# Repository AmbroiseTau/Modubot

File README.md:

<div style="display: flex; justify-content: center; margin: 0 auto; width: 100%;">
  
</div>

---

**Modubot** is a modular robotics platform built around **cube-shaped modules**, each with a **dedicated PCB** designed for specific functions. These modules can serve as **regional controllers**, **motor controllers**, **sensor modules**, or other customizable components, allowing for a **flexible and adaptable robotic system**. The entire project is based on **STM32 microcontrollers**.

<div style="display: flex; justify-content: center; margin: 0 auto; width: 100%;">

</div>

---

## **Goal:**

The vision for Modubot is to create a **flexible, modular platform** that promotes **hands-on learning** and **skill development**. By using **cube-based modules**, each with a unique **electronic function**, Modubot acts as a **test platform** for experimenting with:

- **Protocols**
- **Circuits**
- **PCB architecture**
- **Firmware**

This project is a chance to **apply and refine engineering knowledge** while exploring **creative possibilities in robotics**.

---

## **Roadmap:**
1. **✅ Design First Ever Module (General Purpose) - Accomplished**
2. **✅ Create a Simple 2-Wheel Robot with Remote Operation - Accomplished**
3. **✅ Write Firmware for CAN-FD, IMU, UART GPS**
4. **✅ Create a 2 Degrees of Freedom Arm**
5. **🔲 Design a Brushed/Stepper/BLDC Motor Controller Module (MCM)**
6. **🔲 Create a Miniature Buggy Rover**
7. **🔲 Design 2nd Version of the General Purpose Module (GPM)**
8. **🔲 Design Modular Drone (1x GPM + 4x MCM)**

---

## **Current Status:**

### **STAGE 2:**
The current phase features a **2-wheeled robot** designed as a **proof of concept**. It tests the **General Purpose Module (GPM v1)** along with:

- **SPI to NRF24L01** (used for remote control)
- **Servo control**

However, the **continuous servos** faced **tuning issues**, preventing the robot from driving straight, highlighting the need to shift towards **PID-controlled DC motors with encoders** for precise control.

<div style="display: flex; justify-content: center; margin: 0 auto; width: 100%;">

</div>

---

### **STAGE 1:**
The **first wave of designs** has been completed. The initial **PCB design** was kept **simple** to avoid unnecessary points of failure. It functions as intended, though there are some **design oversights**:

- It cannot handle **high current** (only 1-2 amps at 12V)
- Limited **resistance to back EMF**

These issues will be addressed in **version 2**, after learning more about system requirements.

The **3D-printed structure** has also been refined and is expected to remain unchanged unless major issues arise. For **quick connections** between modules and subcomponents (e.g., PCB bracket), **3D-printed Lego pins (scaled 1.25x)** are being used, and for more **permanent fixtures**, **M6 bolts** can be inserted in the same holes. Initially, **PETG** was used for printing, but due to **brittleness**, the material has been changed to **ABS**, which is more **ductile**.

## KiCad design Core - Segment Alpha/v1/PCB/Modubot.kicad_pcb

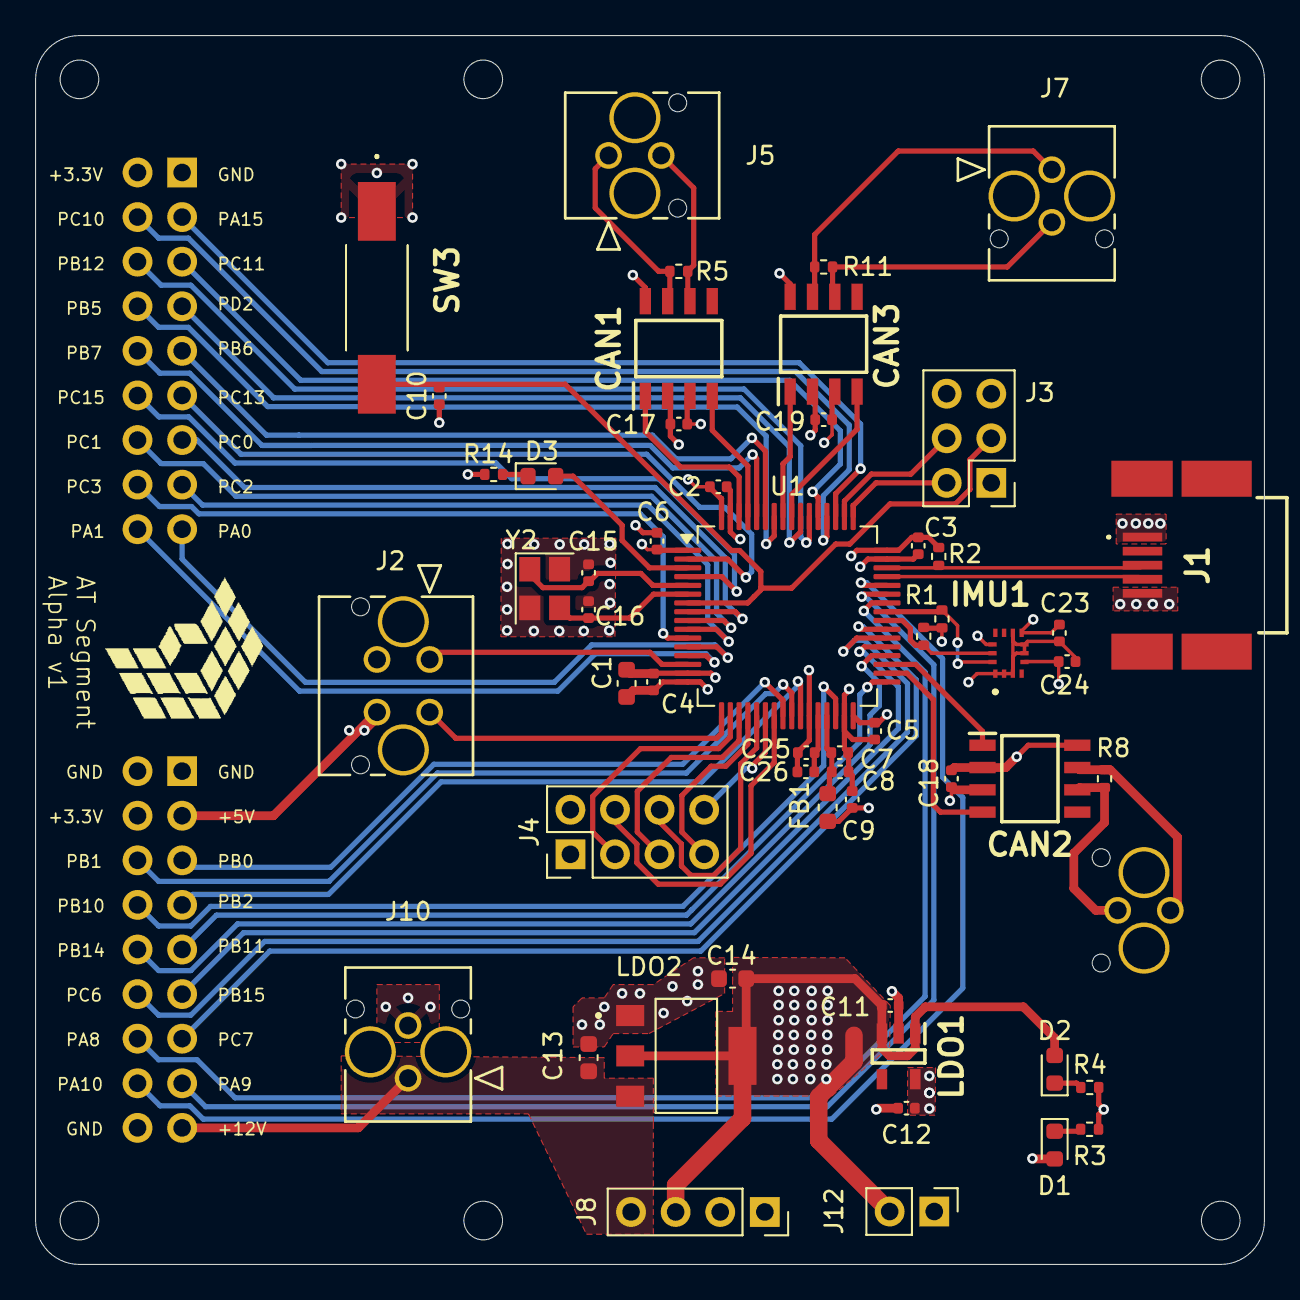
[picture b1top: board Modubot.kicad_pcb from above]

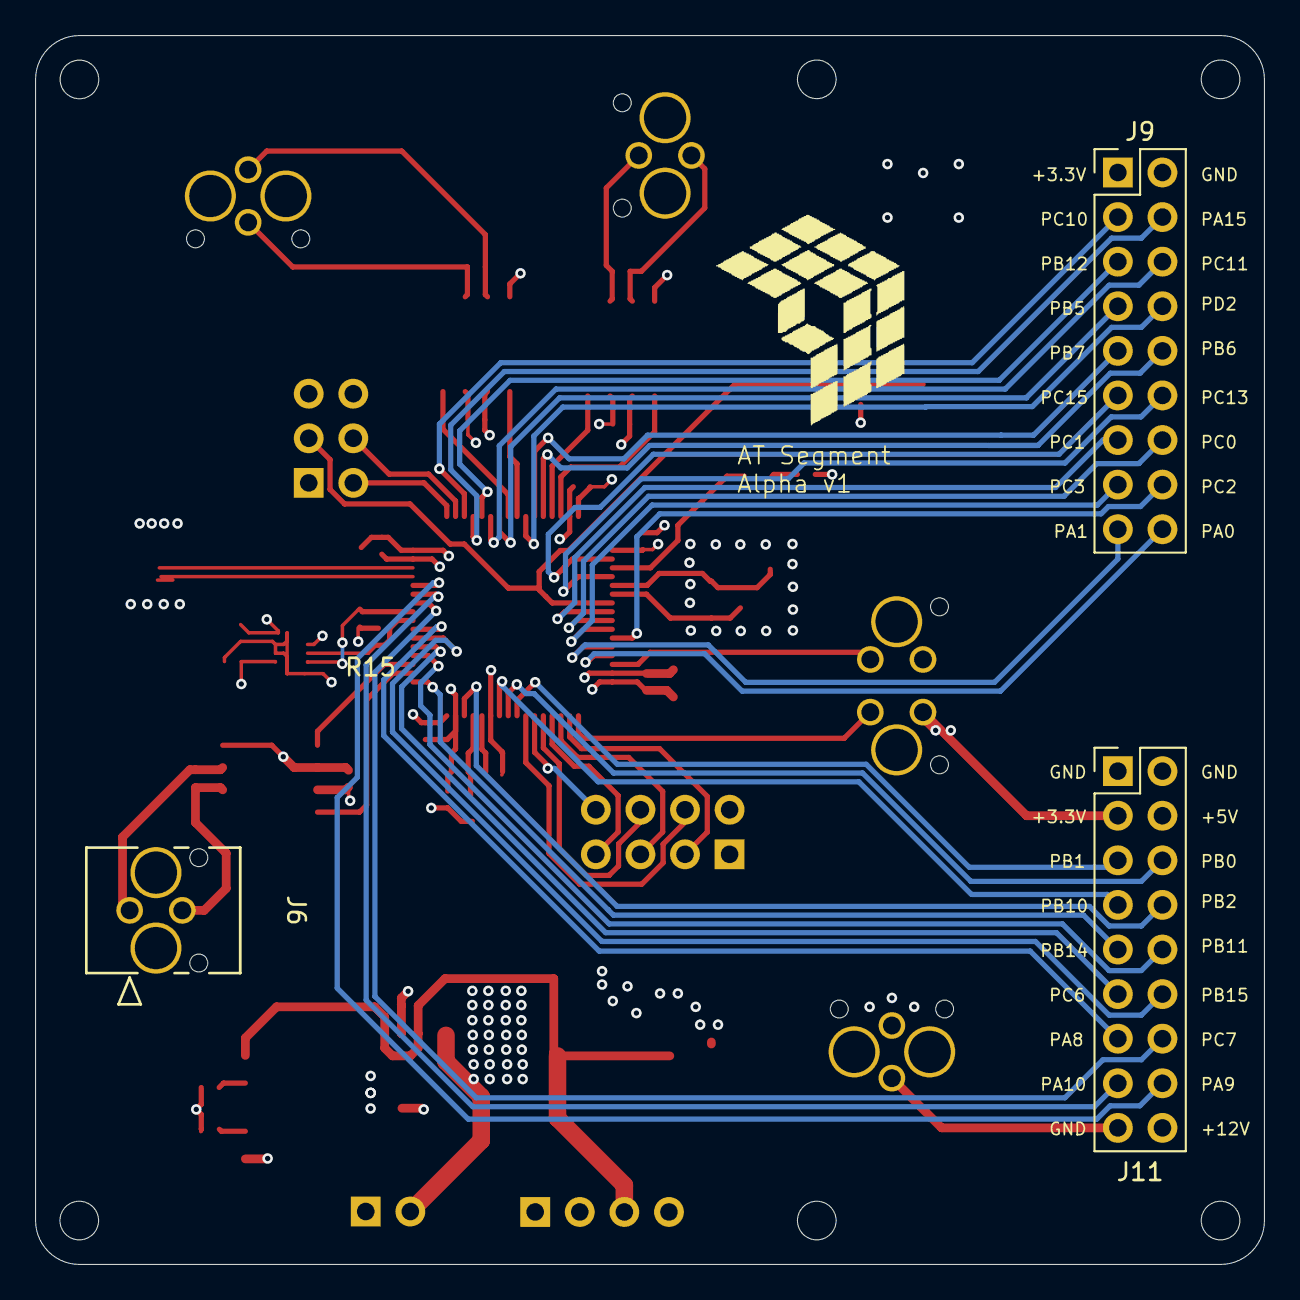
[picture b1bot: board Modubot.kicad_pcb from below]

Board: 4 copper layers, 70.0 x 70.0 mm, 63 parts (3 on the bottom side), 67 nets.

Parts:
C1, C13, C14: 10u; C_0603_1608Metric
C2, C3, C4, C5, C6, C7, C10, C17, C18, C19, C23, C24, C25: 100n; C_0402_1005Metric
C8, C9, C11, C12, C26: 1u; C_0402_1005Metric
C15, C16: 10p; C_0402_1005Metric
CAN1, CAN2, CAN3: MCP2544WFDT-E_SN; SOIC127P600X175-8N
D1, D2, D3: LED; LED_0603_1608Metric
FB1: 120R; L_0603_1608Metric
H1, H2, H3, H3#2, H4, H4#2: MountingHole; MountingHole_2.2mm_M2
IMU1: LSM6DSOTR; LSM6DS3USTR
J1: USB_B_Mini; 548190572
J2: Molex_Mini_2x2; CON_430450424_MOL_VERT_2x2
J3: JTAG; PinHeader_2x03_P2.54mm_Vertical
J4: SPI_NRF; PinHeader_2x04_P2.54mm_Vertical
J5, J6, J7, J10: Molex_Mini_1x2; CON_430450224_MOL_VERT_1x2
J8: Power; PinSocket_1x04_P2.54mm_Vertical
J9: Remaining Pins_2; PinHeader_2x09_P2.54mm_Vertical
J11: Remaining Pins_1; PinHeader_2x09_P2.54mm_Vertical
J12: Conn_01x02_Pin; PinHeader_1x02_P2.54mm_Vertical
LDO1: AP7366EA-33W5-7; SOT95P285X140-5N
LDO2: TS1117BCW50_RPG; VREG_TS1117BCW50_RPG
R1, R2, R3, R4, R14, R15: 1k5; R_0402_1005Metric
R5, R8, R11: 120R; R_0402_1005Metric
SW3: SW_Push; Button_TL3302AF260QG
U1: STM32G483RE; LQFP-64_10x10mm_P0.5mm
Y2: 16MHz; Crystal_SMD_3225-4Pin_3.2x2.5mm

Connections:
+3.3V: C1.1, C2.1, C3.1, C4.1, C5.1, C6.1, C9.1, C12.1, C23.1, C24.1, D1.2 (A), FB1.1, IMU1.5 (VDDIO), IMU1.8 (VDD), IMU1.12 (CS), J3.5, J4.2, J8.2, J9.2, J11.4, LDO1.5 (OUT), R1.1, R2.1, R15.2, U1.1 (VBAT), U1.16 (VDD), U1.32 (VDD), U1.48 (VDD), U1.64 (VDD)
+3.3VA: C7.1, C8.1, C25.1, C26.1, FB1.2, U1.28 (VREF+), U1.29 (VDDA)
+5V: C11.1, C14.1, C17.2, C18.2, C19.2, CAN1.3 (VDD), CAN2.3 (VDD), CAN3.3 (VDD), D2.2 (A), J2.4, J8.3, J11.3, J12.2, LDO1.1 (IN), LDO1.3 (EN), LDO2.2 (OUTPUT), LDO2.4 (OUTPUT)
+12V: C13.1, J8.4, J10.1, J11.17, LDO2.3 (INPUT)
/3V3_LED_C: D1.1 (K), R3.1
/5V_LED_C: D2.1 (K), R4.1
/CANH_1: CAN1.7 (CANH), J5.1, R5.1
/CANH_2: CAN2.7 (CANH), J6.1, R8.1
/CANH_3: CAN3.7 (CANH), J7.1, R11.1
/CANL_1: CAN1.6 (CANL), J5.2, R5.2
/CANL_2: CAN2.6 (CANL), J6.2, R8.2
/CANL_3: CAN3.6 (CANL), J7.2, R11.2
/FDCAN1_RX: CAN1.4 (RXD), U1.61 (PB8)
/FDCAN1_TX: CAN1.1 (TXD), U1.62 (PB9)
/FDCAN2_RX: CAN2.4 (RXD), U1.34 (PB12)
/FDCAN2_TX: CAN2.1 (TXD), U1.35 (PB13)
/FDCAN3_RX: CAN3.4 (RXD), U1.56 (PB3)
/FDCAN3_TX: CAN3.1 (TXD), U1.57 (PB4)
/GPIO_CE: J4.3, U1.18 (PA4)
/GPIO_CSN: J4.4, U1.23 (PC5)
/GPIO_IRQ: J4.8, U1.22 (PC4)
/I2C3_SCL: IMU1.13 (SCL), R15.1, U1.40 (PC8)
/I2C3_SDA: IMU1.14 (SDA), R1.2, U1.41 (PC9)
/NRST: C10.1, J3.3, SW3.2, U1.7 (PG10)
/PA0: J9.17, U1.12 (PA0)
/PA1: J9.18, U1.13 (PA1)
/PA8: J11.14, U1.42 (PA8)
/PA9: J11.15, U1.43 (PA9)
/PA10: J11.16, U1.44 (PA10)
/PA15: J9.3, U1.51 (PA15)
/PB0: J11.5, U1.24 (PB0)
/PB1: J11.6, U1.25 (PB1)
/PB2: J11.7, U1.26 (PB2)
/PB5: J9.8, U1.58 (PB5)
/PB6: J9.9, U1.59 (PB6)
/PB7: J9.10, U1.60 (PB7)
/PB10: J11.8, U1.30 (PB10)
/PB11: J11.9, U1.33 (PB11)
/PB14: J11.10, U1.36 (PB14)
/PB15: J11.11, U1.37 (PB15)
/PC0: J9.13, U1.8 (PC0)
/PC1: J9.14, U1.9 (PC1)
/PC2: J9.15, U1.10 (PC2)
/PC3: J9.16, U1.11 (PC3)
/PC6: J11.12, U1.38 (PC6)
/PC7: J11.13, U1.39 (PC7)
/PC10: J9.4, U1.52 (PC10)
/PC11: J9.5, U1.53 (PC11)
/PC12: J9.6, U1.54 (PC12)
/PC13: J9.11, U1.2 (PC13)
/PC15: J9.12, U1.4 (PC15)
/PD2: J9.7, U1.55 (PD2)
/RCC_OSC_IN: C15.1, U1.5 (PF0), Y2.1
/RCC_OSC_OUT: C16.1, U1.6 (PF1), Y2.3
/SPI1_MISO: J4.7, U1.20 (PA6)
/SPI1_MOSI: J4.6, U1.21 (PA7)
/SPI1_SCK: J4.5, U1.19 (PA5)
/SYS_JTCK-SWCLK: J3.4, U1.50 (PA14)
/SYS_JTMS-SWDIO: J3.2, U1.49 (PA13)
/USART2_RX: J2.2, U1.17 (PA3)
/USART2_TX: J2.1, U1.14 (PA2)
/USB_D+: J1.3 (D+), R2.2, U1.46 (PA12)
/USB_D-: J1.4 (D-), U1.45 (PA11)
/User_LED_C: D3.1 (K), R14.1
/User_LED_GPIO: D3.2 (A), U1.3 (PC14)
GND: C1.2, C2.2, C3.2, C4.2, C5.2, C6.2, C7.2, C8.2, C9.2, C10.2, C11.2, C12.2, C13.2, C14.2, C15.2, C16.2, C17.1, C18.1, C19.1, C23.2, C24.2, C25.2, C26.2, CAN1.2 (VSS), CAN1.8 (STBY), CAN2.2 (VSS), CAN2.8 (STBY), CAN3.2 (VSS), CAN3.8 (STBY), IMU1.1 (SDO/SA0), IMU1.2 (SDX), IMU1.3 (SCX), IMU1.6 (GND_1), IMU1.7 (GND_2), IMU1.9 (INT2), J1.1 (GND), J2.3, J3.1, J3.6, J4.1, J8.1, J9.1, J10.2, J11.1, J11.2, J11.18, LDO1.2 (GND), LDO2.1 (FIXED), R3.2, R4.2, R14.2, SW3.1, U1.15 (VSS), U1.27 (VSSA), U1.31 (VSS), U1.47 (VSS), U1.63 (VSS), Y2.2, Y2.4
VBUS: J1.5 (VBUS), J12.1

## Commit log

2024-09-09 First PCB Cad
2024-09-24 Added Images
